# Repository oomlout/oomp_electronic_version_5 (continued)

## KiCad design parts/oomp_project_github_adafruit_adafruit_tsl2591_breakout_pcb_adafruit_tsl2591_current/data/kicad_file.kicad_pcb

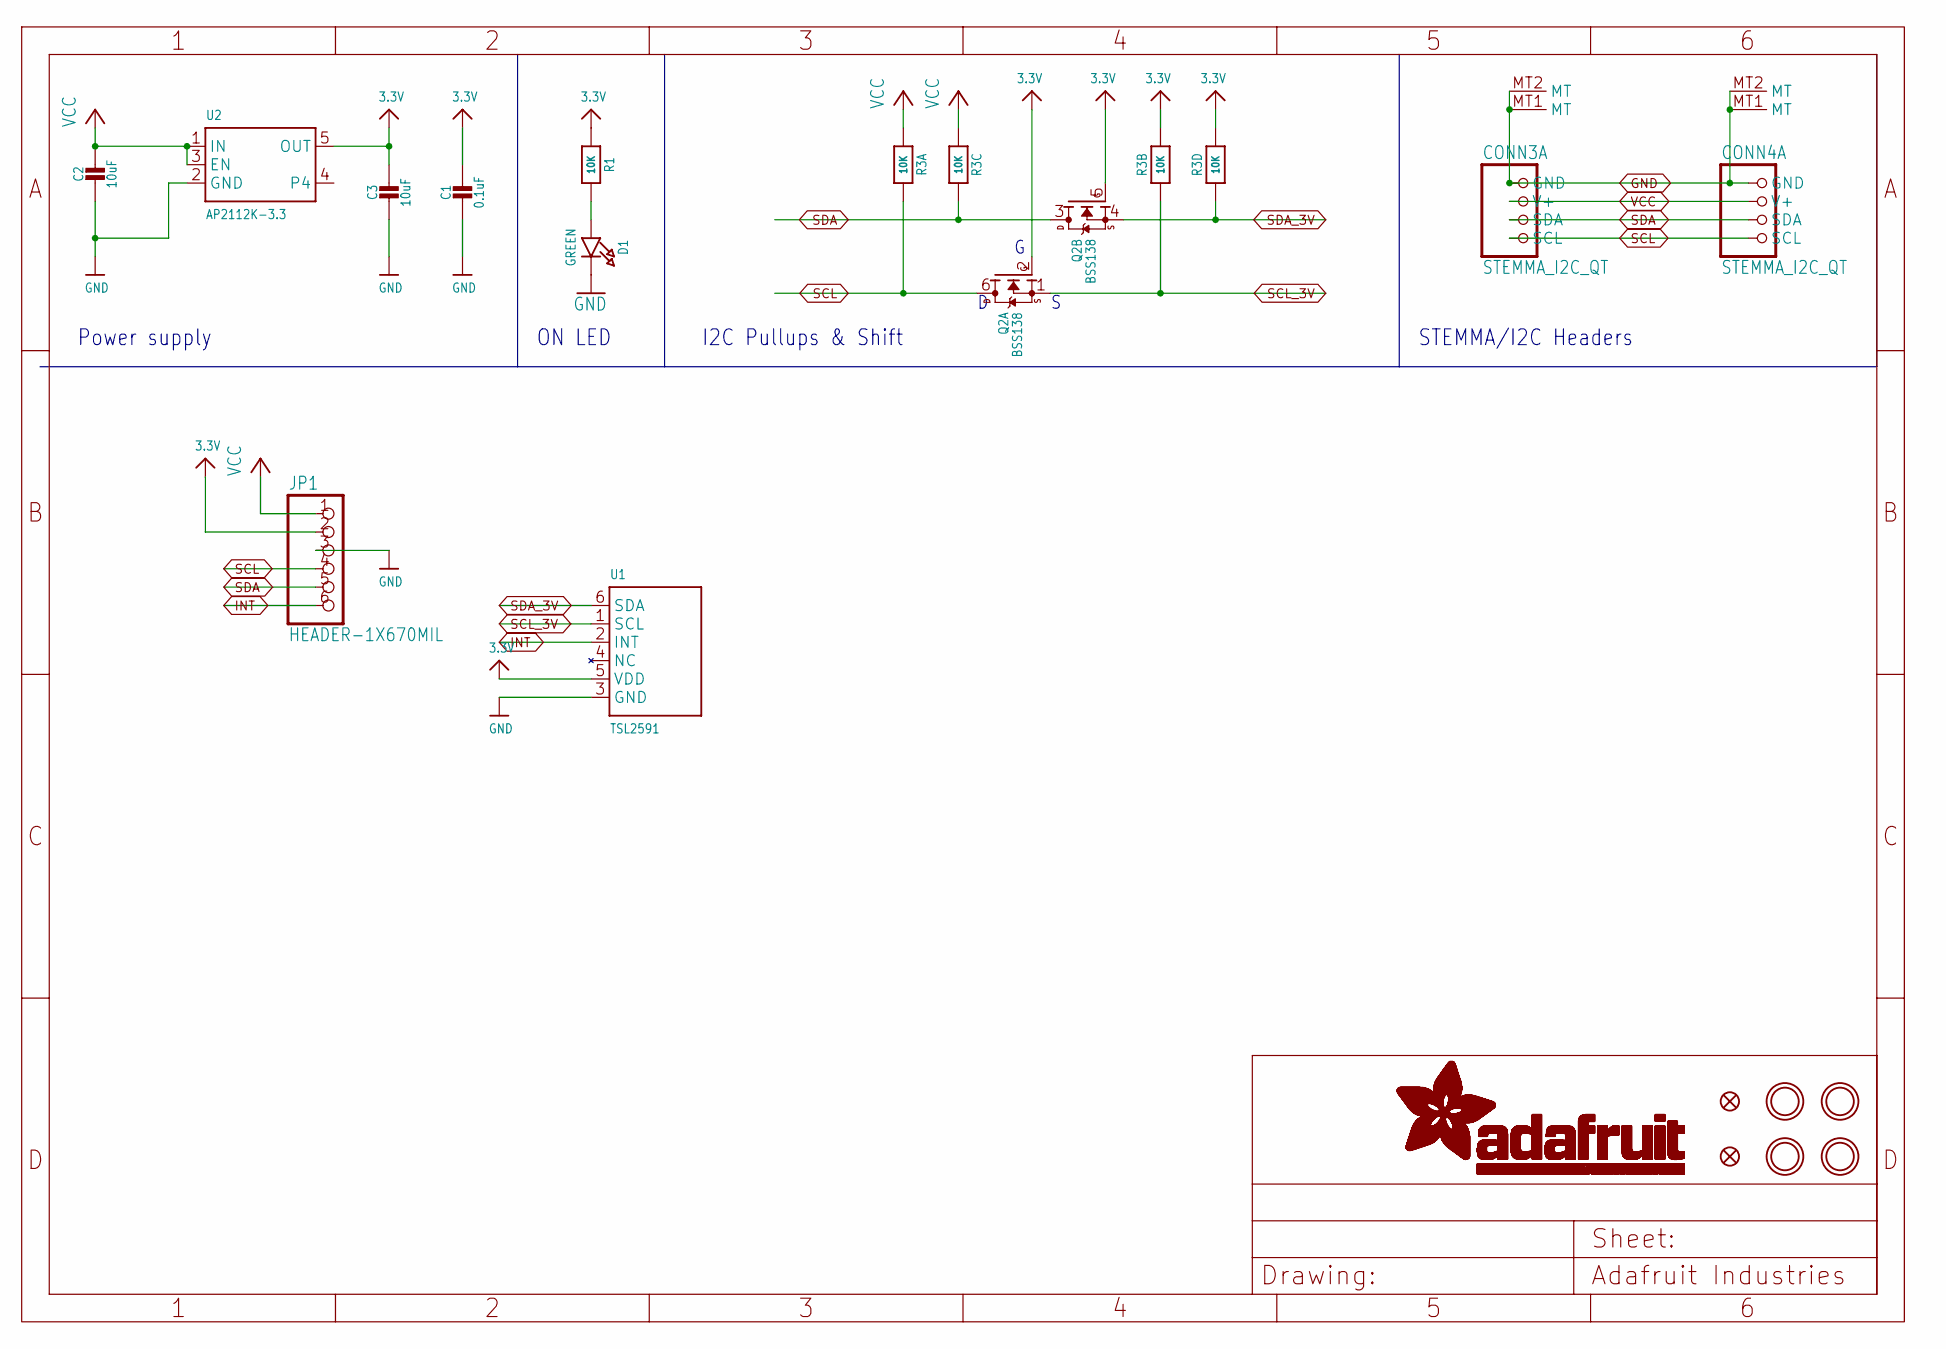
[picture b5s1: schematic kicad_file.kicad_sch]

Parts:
C1: 0.1uF; 0603-NO
C2, C3: 10uF; 0805-NO
CONN3, CONN4: STEMMA_I2C_QT; JST_SH4
D1: GREEN; CHIPLED_0603_NOOUTLINE
FID3, FID4: FIDUCIAL_1MM
JP1: HEADER-1X670MIL; 1X06_ROUND_70
Q2: BSS138; SOT363
R1: 10K; 0603-NO
R3: 10K; RESPACK_4X0603
U1: TSL2591; DFN6_TAOS
U2: AP2112K-3.3; SOT23-5
U$1, U$17, U$19, U$21: MOUNTINGHOLE2.5; MOUNTINGHOLE_2.5_PLATED

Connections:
3.3V: C1.1, C3.1, JP1.2, Q2.2 (G), Q2.5 (G), R1.1, R3.2 (1), R3.4 (1), U1.5 (VDD), U2.5 (OUT)
GND: C1.2, C2.2, C3.2, CONN3.1 (GND), CONN3.MT1 (MT), CONN3.MT2 (MT), CONN4.1 (GND), CONN4.MT1 (MT), CONN4.MT2 (MT), D1.C, JP1.3, U1.3 (GND), U2.2 (GND)
INT: JP1.6, U1.2 (INT)
unnamed: D1.A, R1.2
SCL: CONN3.4 (SCL), CONN4.4 (SCL), JP1.4, Q2.6 (D), R3.8 (2)
SCL_3V: Q2.1 (S), R3.7 (2), U1.1 (SCL)
SDA: CONN3.3 (SDA), CONN4.3 (SDA), JP1.5, Q2.3 (D), R3.6 (2)
SDA_3V: Q2.4 (S), R3.5 (2), U1.6 (SDA)
VCC: C2.1, CONN3.2 (V+), CONN4.2 (V+), JP1.1, R3.1, R3.3 (1), U2.1 (IN), U2.3 (EN)

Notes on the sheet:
I2C Pullups & Shift
Power supply
ON LED
STEMMA/I2C Headers

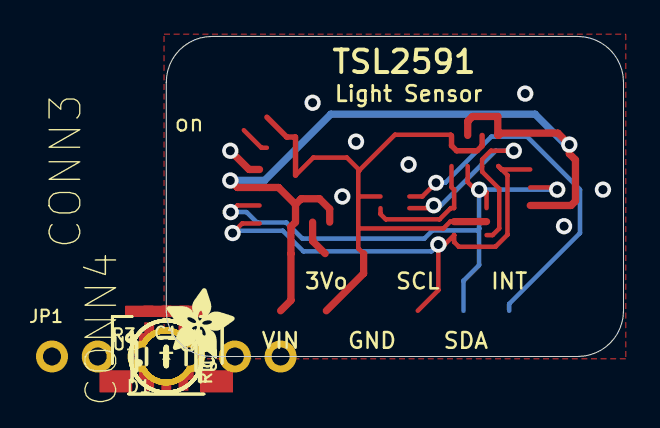
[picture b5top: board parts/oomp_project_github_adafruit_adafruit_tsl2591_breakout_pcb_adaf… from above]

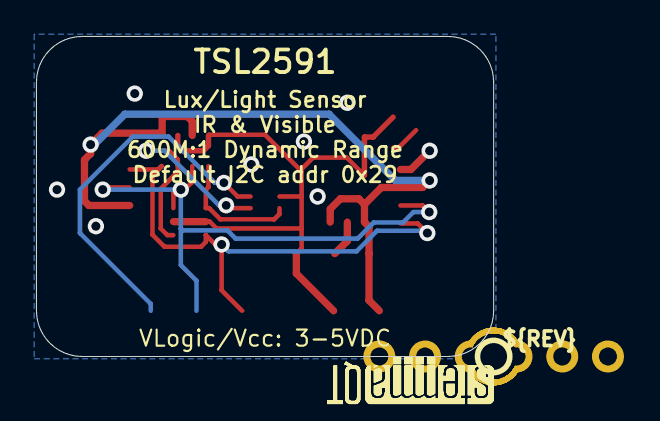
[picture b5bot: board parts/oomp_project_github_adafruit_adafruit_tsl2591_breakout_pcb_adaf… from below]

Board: 2 copper layers, 25.4 x 17.8 mm, 22 parts (3 on the bottom side), 9 nets.

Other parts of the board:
U$22: ADAFRUIT_3.5MM
U$25: PCBFEAT-REV-040
U$30, U$31: STEMMAQT

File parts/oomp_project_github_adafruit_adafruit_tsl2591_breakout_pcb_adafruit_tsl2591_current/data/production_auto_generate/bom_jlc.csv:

Comment,Designator,Footprint,LCSC Part #
,JP1,Adafruit TSL2591-import-fps:1X06_ROUND_70,C37208
,U$22,Adafruit TSL2591-import-fps:ADAFRUIT_3.5MM,
,U$25,Adafruit TSL2591-import-fps:PCBFEAT-REV-040,
,"U$30,U$31",Adafruit TSL2591-import-fps:STEMMAQT,
0.1uF,C1,Adafruit TSL2591-import-fps:0603-NO,C14663
10K,R1,Adafruit TSL2591-import-fps:0603-NO,C98220
10K,R3,Adafruit TSL2591-import-fps:RESPACK_4X0603,C98220
10uF,"C2,C3",Adafruit TSL2591-import-fps:0805-NO,
AP2112K-3.3,U2,Adafruit TSL2591-import-fps:SOT23-5,
BSS138,Q2,Adafruit TSL2591-import-fps:SOT363,
GREEN,D1,Adafruit TSL2591-import-fps:CHIPLED_0603_NOOUTLINE,
STEMMA_I2C_QT,"CONN3,CONN4",Adafruit TSL2591-import-fps:JST_SH4,C160404
TSL2591,U1,Adafruit TSL2591-import-fps:DFN6_TAOS,

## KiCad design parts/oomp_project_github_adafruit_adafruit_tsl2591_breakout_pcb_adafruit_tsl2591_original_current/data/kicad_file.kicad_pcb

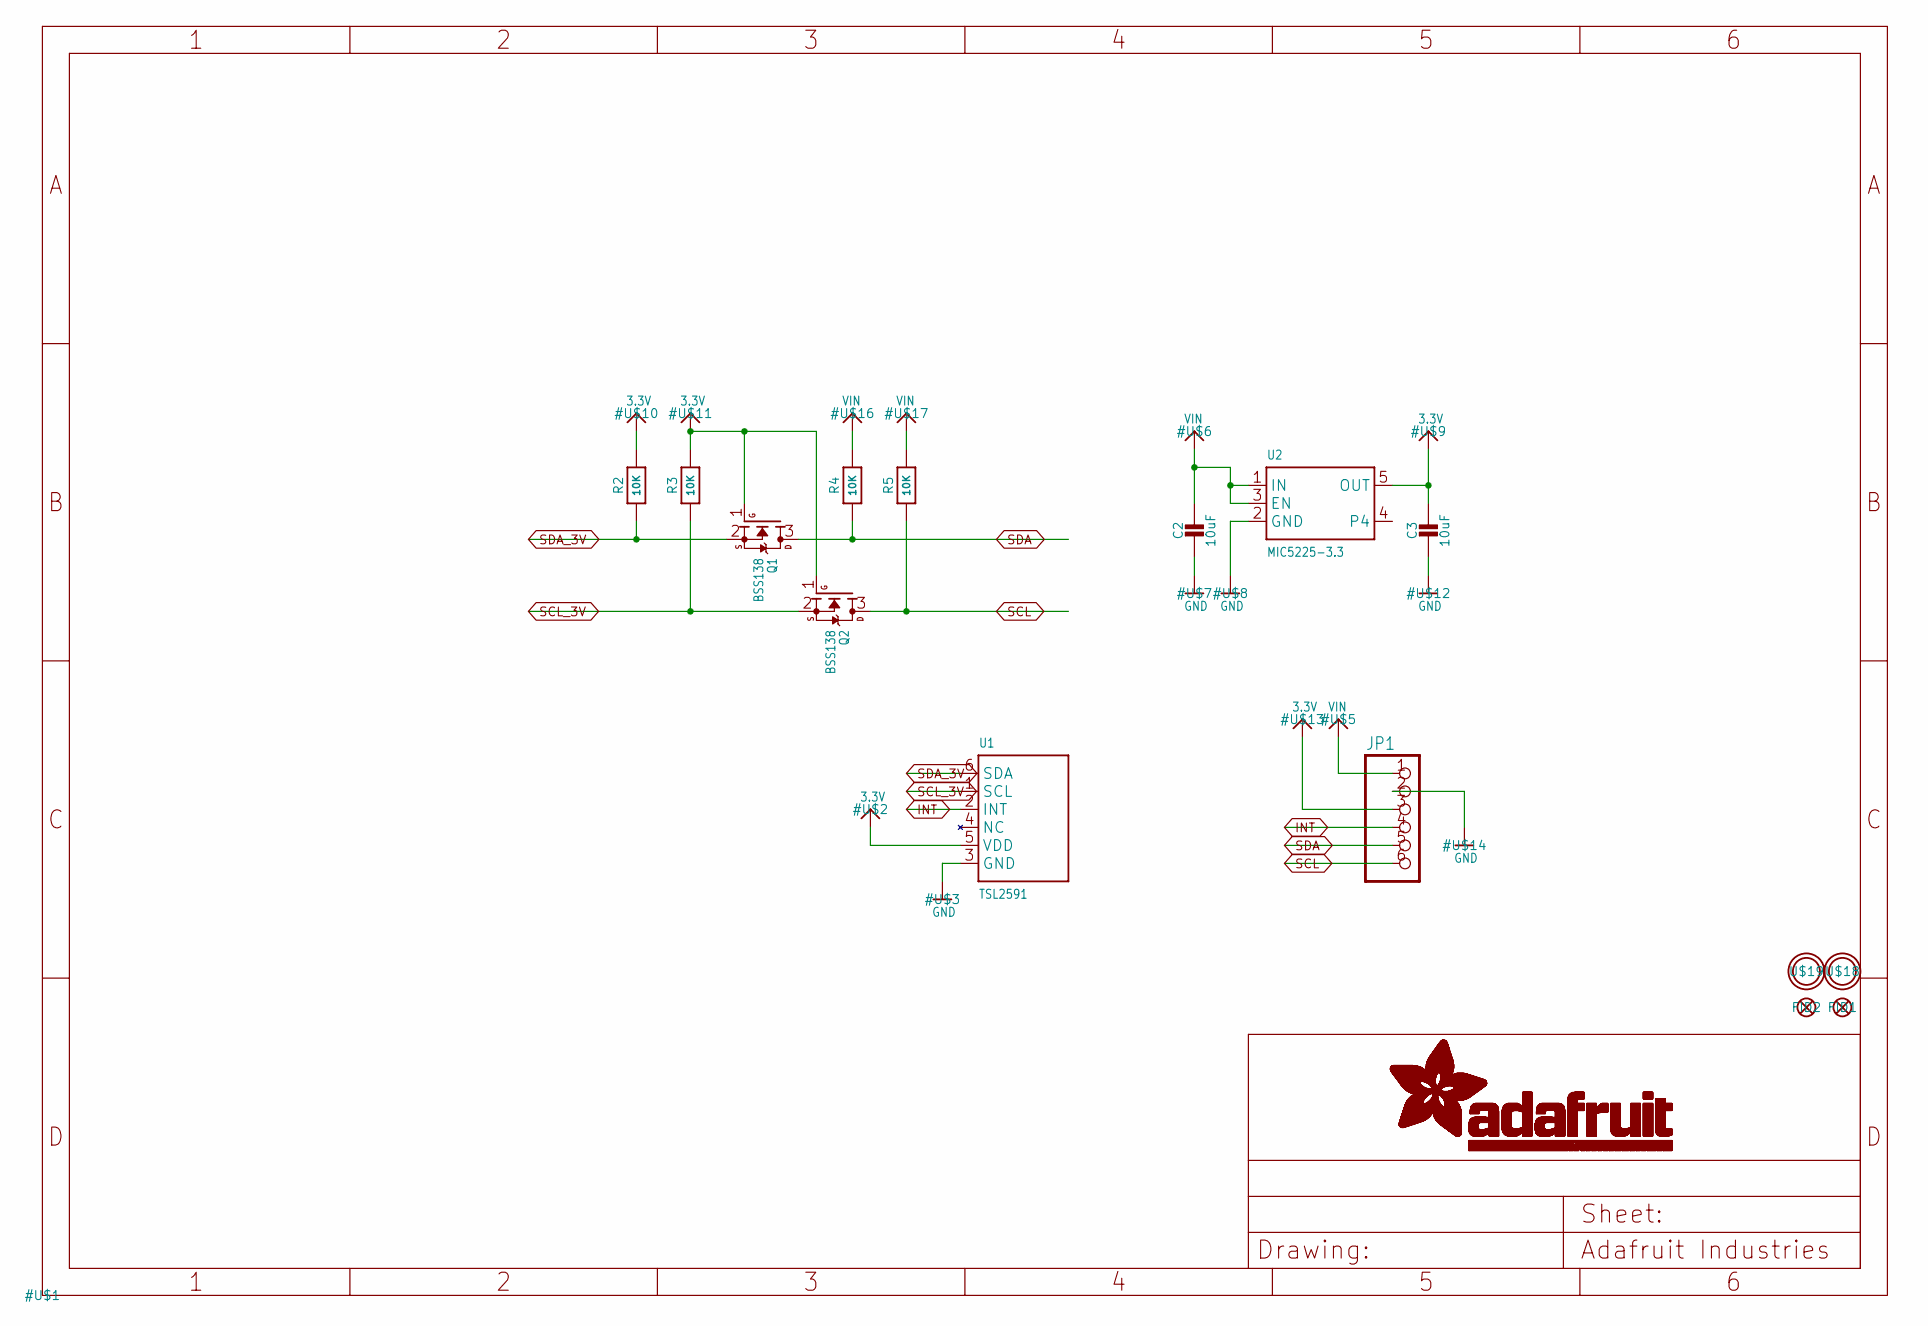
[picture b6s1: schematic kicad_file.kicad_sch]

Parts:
C2, C3: 10uF; 0805-NO
FID1, FID2: FIDUCIAL""; FIDUCIAL_1MM
JP1: HEADER-1X676MIL_FULLROUND; 1X06_ROUND_FULL_76
Q1, Q2: BSS138; SOT23-WIDE
R2, R3, R4: 10K; 0805-NO
R5: 10K; _0805MP
U1: TSL2591; DFN6_TAOS
U2: MIC5225-3.3; SOT23-5
U$18, U$19: MOUNTINGHOLE2.5; MOUNTINGHOLE_2.5_PLATED

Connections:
3.3V: C3.1, JP1.3, Q1.1 (G), Q2.1 (G), R2.2, R3.2, U1.5 (VDD), U2.5 (OUT)
GND: C2.2, C3.2, JP1.2, U1.3 (GND), U2.2 (GND)
INT: JP1.4, U1.2 (INT)
SCL: JP1.6, Q2.3 (D), R5.1
SCL_3V: Q2.2 (S), R3.1, U1.1 (SCL)
SDA: JP1.5, Q1.3 (D), R4.1
SDA_3V: Q1.2 (S), R2.1, U1.6 (SDA)
VIN: C2.1, JP1.1, R4.2, R5.2, U2.1 (IN), U2.3 (EN)

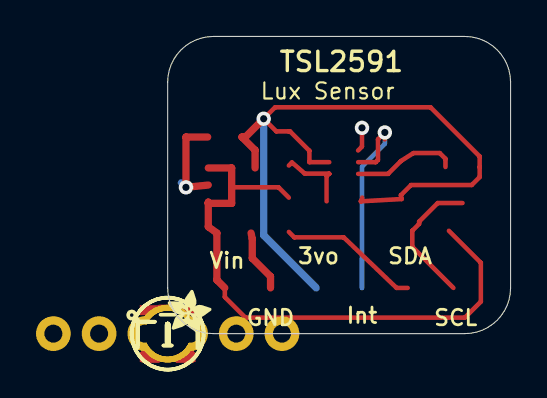
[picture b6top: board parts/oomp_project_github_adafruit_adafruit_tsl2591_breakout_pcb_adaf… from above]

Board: 2 copper layers, 19.1 x 16.5 mm, 17 parts (1 on the bottom side), 8 nets.

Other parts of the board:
U$15: ADAFRUIT_2.5MM
U$20: ADAFRUIT_5MM

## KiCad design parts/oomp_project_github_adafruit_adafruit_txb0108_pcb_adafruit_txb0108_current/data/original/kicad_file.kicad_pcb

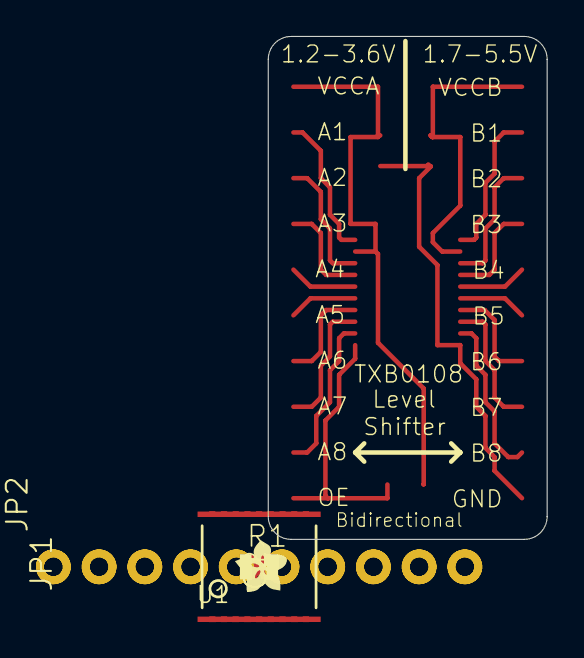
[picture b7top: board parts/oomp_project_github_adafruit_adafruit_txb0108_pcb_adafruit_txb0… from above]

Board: 16 copper layers, 15.5 x 27.9 mm, 8 parts (0 on the bottom side), 20 nets.

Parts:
C1, C2: 0.1uF; C0805
JP1, JP2: 1X10_ROUND_76
R1: 10K; R0805
U1: TXB0108PWR; TSSOP20
U$4: ADAFRUIT200MIL
U$6: FIDUCIAL; FIDUCIAL_1MM

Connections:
GND: C1.2, C2.2, JP1.10, U1.11
unnamed: JP1.9, U1.12
unnamed: JP1.8, U1.13
unnamed: JP1.7, U1.14
unnamed: JP1.6, U1.15
unnamed: JP1.5, U1.16
unnamed: JP1.4, U1.17
unnamed: JP1.3, U1.18
unnamed: JP1.2, U1.20
unnamed: C2.1, JP1.1, U1.19
unnamed: C1.1, JP2.10, R1.2, U1.2
unnamed: JP2.9, U1.1
unnamed: JP2.8, U1.3
unnamed: JP2.7, U1.4
unnamed: JP2.6, U1.5
unnamed: JP2.5, U1.6
unnamed: JP2.4, U1.7
unnamed: JP2.3, U1.8
unnamed: JP2.2, U1.9
unnamed: JP2.1, R1.1, U1.10
